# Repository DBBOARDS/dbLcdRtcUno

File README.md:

# dbLcdRtcUno
These are the Eagle files for the DB LCD RTC UNO

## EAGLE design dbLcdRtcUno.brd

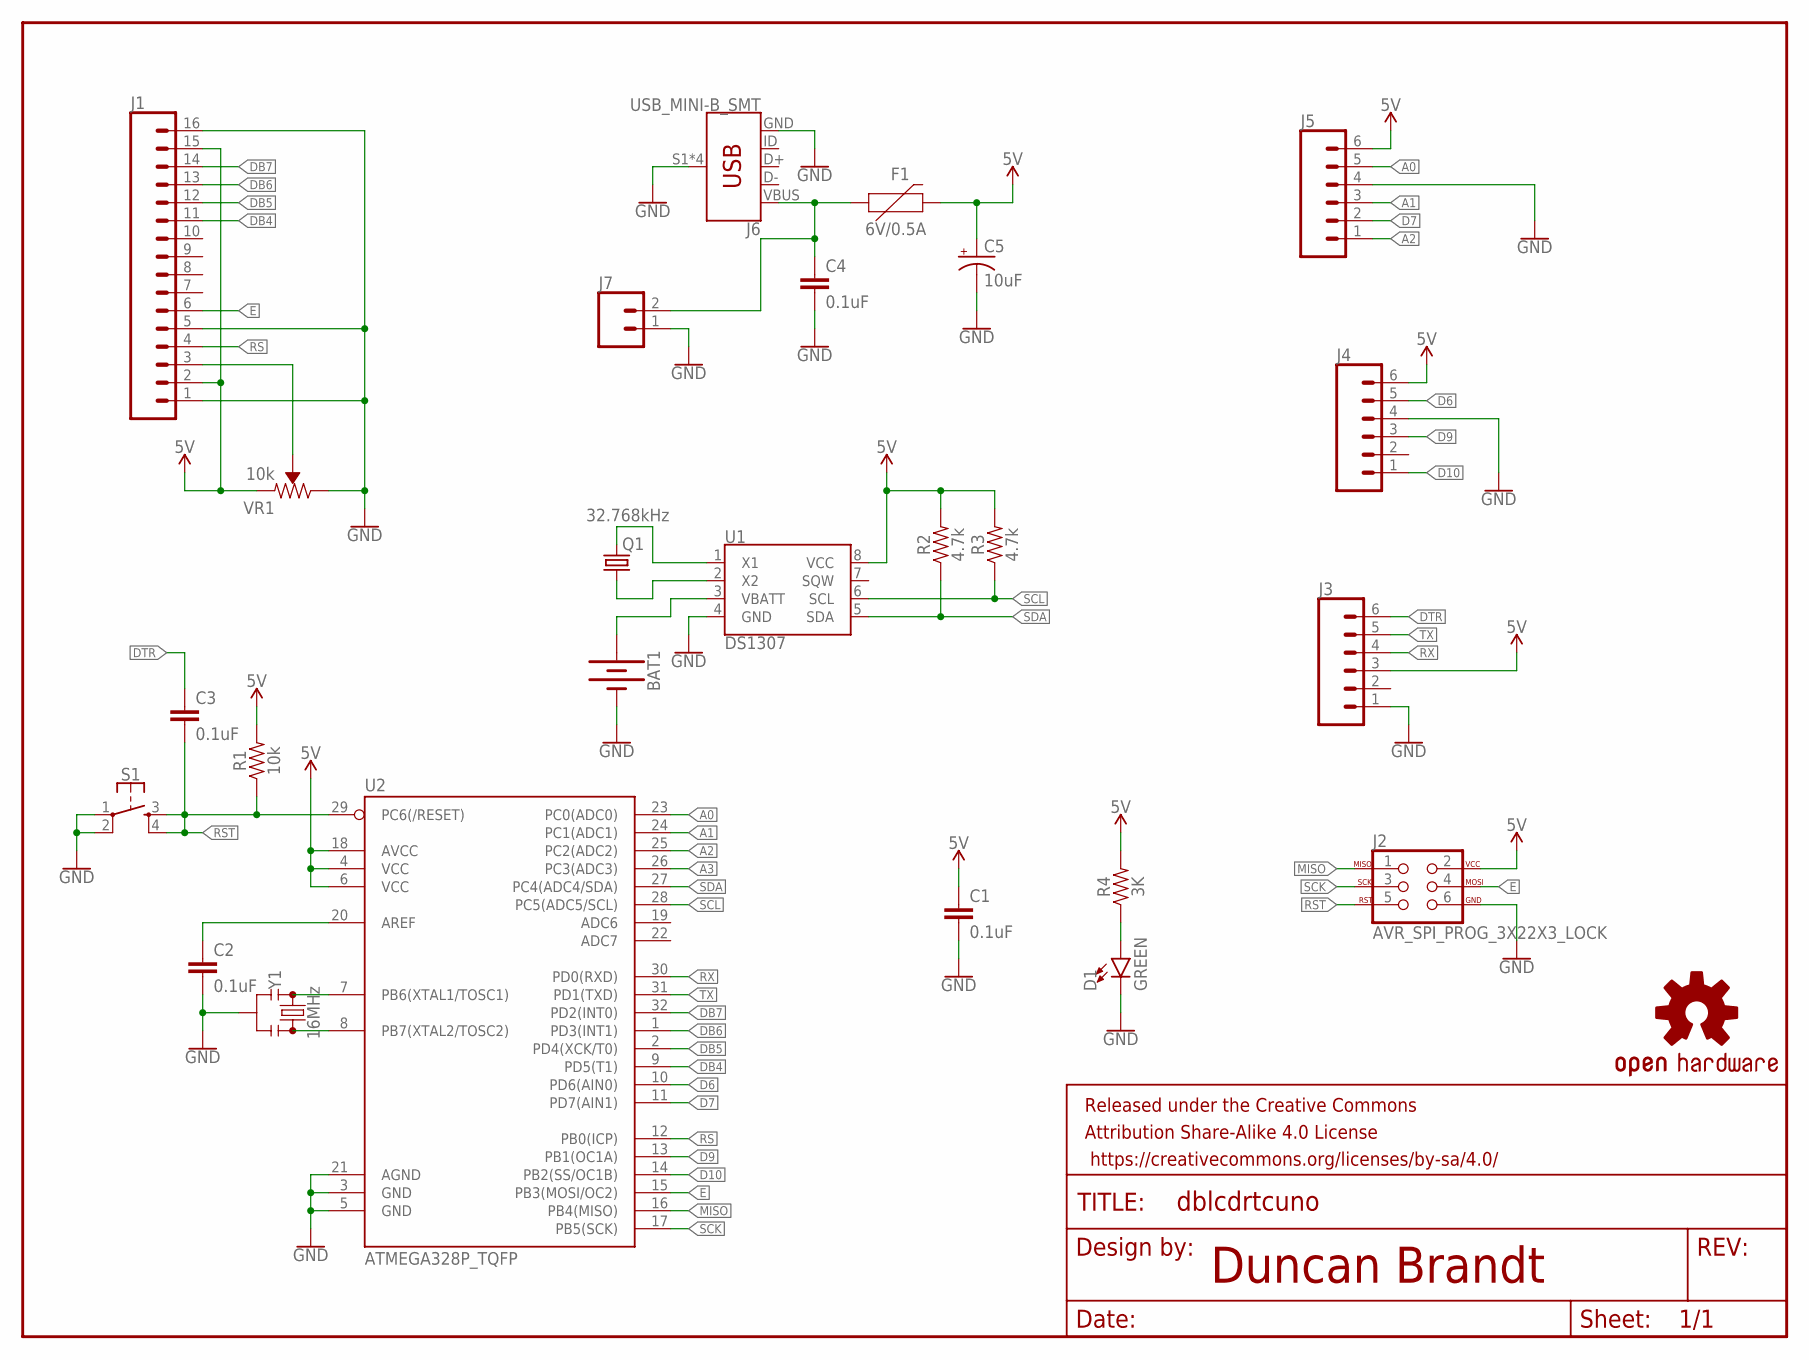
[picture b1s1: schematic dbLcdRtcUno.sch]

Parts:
BAT1: BATTERY-12MM_PTH; BATTCON_12MM_PTH
C1, C2, C3, C4: 0.1uF; 0603
C5: 10uF; EIA3216
D1: GREEN; LED-1206
F1: 6V/0.5A; 1206
FRAME1: FRAME-LETTER; CREATIVE_COMMONS
J1: CONN_16; 1X16
J2: AVR_SPI_PROG_3X22X3_LOCK; 2X3_LOCK
J3, J4, J5: CONN_06SILK_FEMALE_PTH; 1X06
J6: USB_MINI-B_SMT; USB-MINIB
J7: CONN_02; 1X02
LOGO1: OSHW-LOGOL; OSHW-LOGO-L
Q1: 32.768kHz; CRYSTAL-SMD-2X6-CYL
R1: 10k; 0603
R2, R3: 4.7k; 0603
R4: 3K; 0603
S1: MOMENTARY-SWITCH-SPST-2-SMD-5.2MM; TACTILE_SWITCH_SMD_5.2MM
U1: DS1307; SO08-0.15
U2: ATMEGA328P_TQFP; TQFP32-08
VR1: 10k; TRIMPOT-SMD-3MM-CLOSED
Y1: 16MHz; RESONATOR-SMD-3.2X1.3

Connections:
5V: C1.1, C5.+, F1.2, J1.2, J1.15, J2.2, J3.3, J4.6, J5.6, R1.2, R2.2, R3.2, R4.2, U1.8 (VCC), U2.4 (VCC), U2.6 (VCC), U2.18 (AVCC), VR1.1 (CCW)
A0: J5.5, U2.23 (PC0(ADC0))
A1: J5.3, U2.24 (PC1(ADC1))
A2: J5.1, U2.25 (PC2(ADC2))
A3: U2.26 (PC3(ADC3))
D6: J4.5, U2.10 (PD6(AIN0))
D7: J5.2, U2.11 (PD7(AIN1))
D9: J4.3, U2.13 (PB1(OC1A))
D10: J4.1, U2.14 (PB2(SS/OC1B))
DB4: J1.11, U2.9 (PD5(T1))
DB5: J1.12, U2.2 (PD4(XCK/T0))
DB6: J1.13, U2.1 (PD3(INT1))
DB7: J1.14, U2.32 (PD2(INT0))
DTR: C3.1, J3.6
E: J1.6, J2.4, U2.15 (PB3(MOSI/OC2))
GND: BAT1.GND (-), C1.2, C2.2, C4.2, C5.-, D1.C, J1.1, J1.5, J1.16, J2.6, J3.1, J4.4, J5.4, J6.GND, J6.S1 (SHIELD), J6.S2 (SHIELD), J6.S3 (SHIELD), J6.S4 (SHIELD), J7.1, S1.1, S1.2, U1.4 (GND), U2.3 (GND), U2.5 (GND), U2.21 (AGND), VR1.3 (CW), Y1.2
MISO: J2.1, U2.16 (PB4(MISO))
unnamed: Q1.X2 (2), U1.1 (X1)
unnamed: Q1.X1 (1), U1.2 (X2)
unnamed: U2.7 (PB6(XTAL1/TOSC1)), Y1.1
unnamed: BAT1.VCC@1 (+), U1.3 (VBATT)
unnamed: U2.8 (PB7(XTAL2/TOSC2)), Y1.3
unnamed: J1.3, VR1.2 (WIPER)
unnamed: D1.A, R4.1
unnamed: C2.1, U2.20 (AREF)
RS: J1.4, U2.12 (PB0(ICP))
RST: C3.2, J2.5, R1.1, S1.3, S1.4, U2.29 (PC6(/RESET))
RX: J3.4, U2.30 (PD0(RXD))
SCK: J2.3, U2.17 (PB5(SCK))
SCL: R3.1, U1.6 (SCL), U2.28 (PC5(ADC5/SCL))
SDA: R2.1, U1.5 (SDA), U2.27 (PC4(ADC4/SDA))
TX: J3.5, U2.31 (PD1(TXD))
VBUS: C4.1, F1.1, J6.VBUS, J7.2

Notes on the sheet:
Duncan Brandt

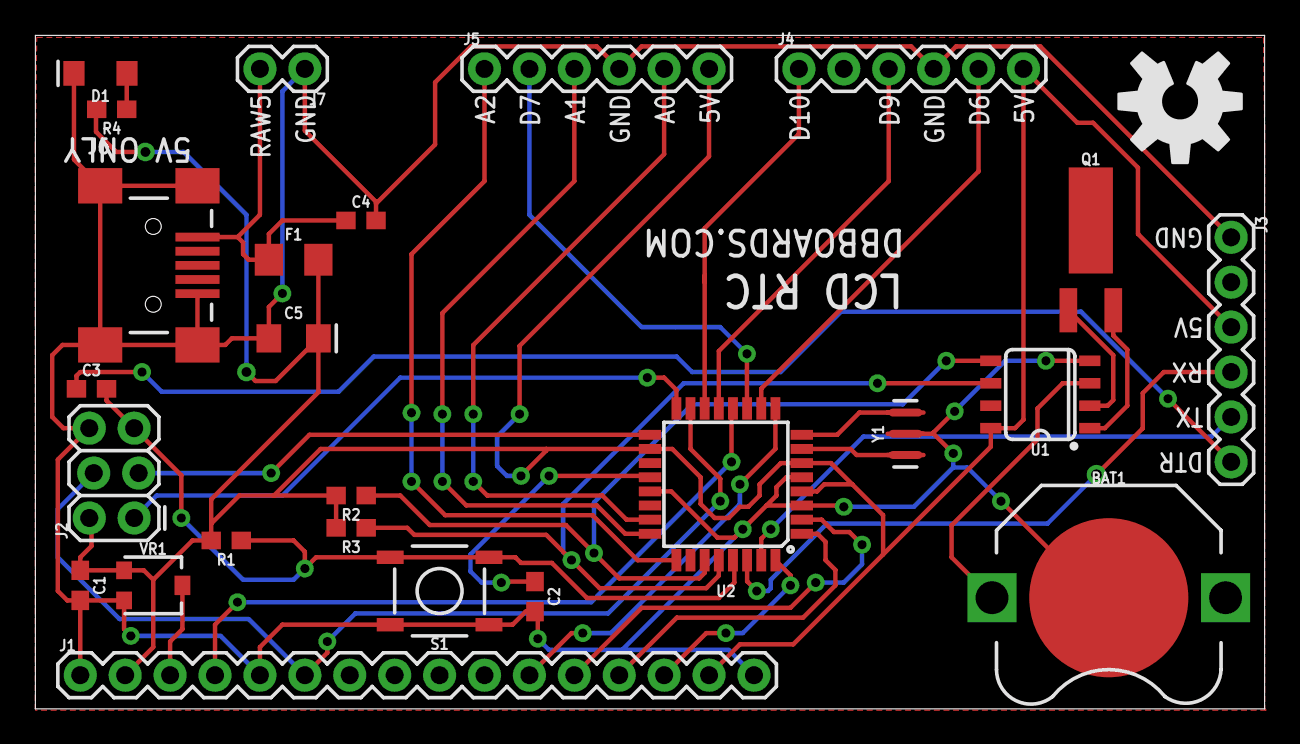
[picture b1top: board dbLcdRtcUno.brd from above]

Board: 2 copper layers, 69.5 x 38.1 mm, 28 parts (1 on the bottom side), 32 nets.

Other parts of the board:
LOGO2: OSHW-LOGOL; OSHW-LOGO-L

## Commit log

2018-03-01 Eagle Files

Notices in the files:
parts and their libraries:
DB-IC-Microcontroller: Licensing: Creative Commons ShareAlike 4.0 International - https://creativecommons.org/licenses/by-sa/4.0
DB-SYMBOLS: Released under the Creative Commons Attribution Share-Alike 4.0 License
DB-SYMBOLS: https://creativecommons.org/licenses/by-sa/4.0
